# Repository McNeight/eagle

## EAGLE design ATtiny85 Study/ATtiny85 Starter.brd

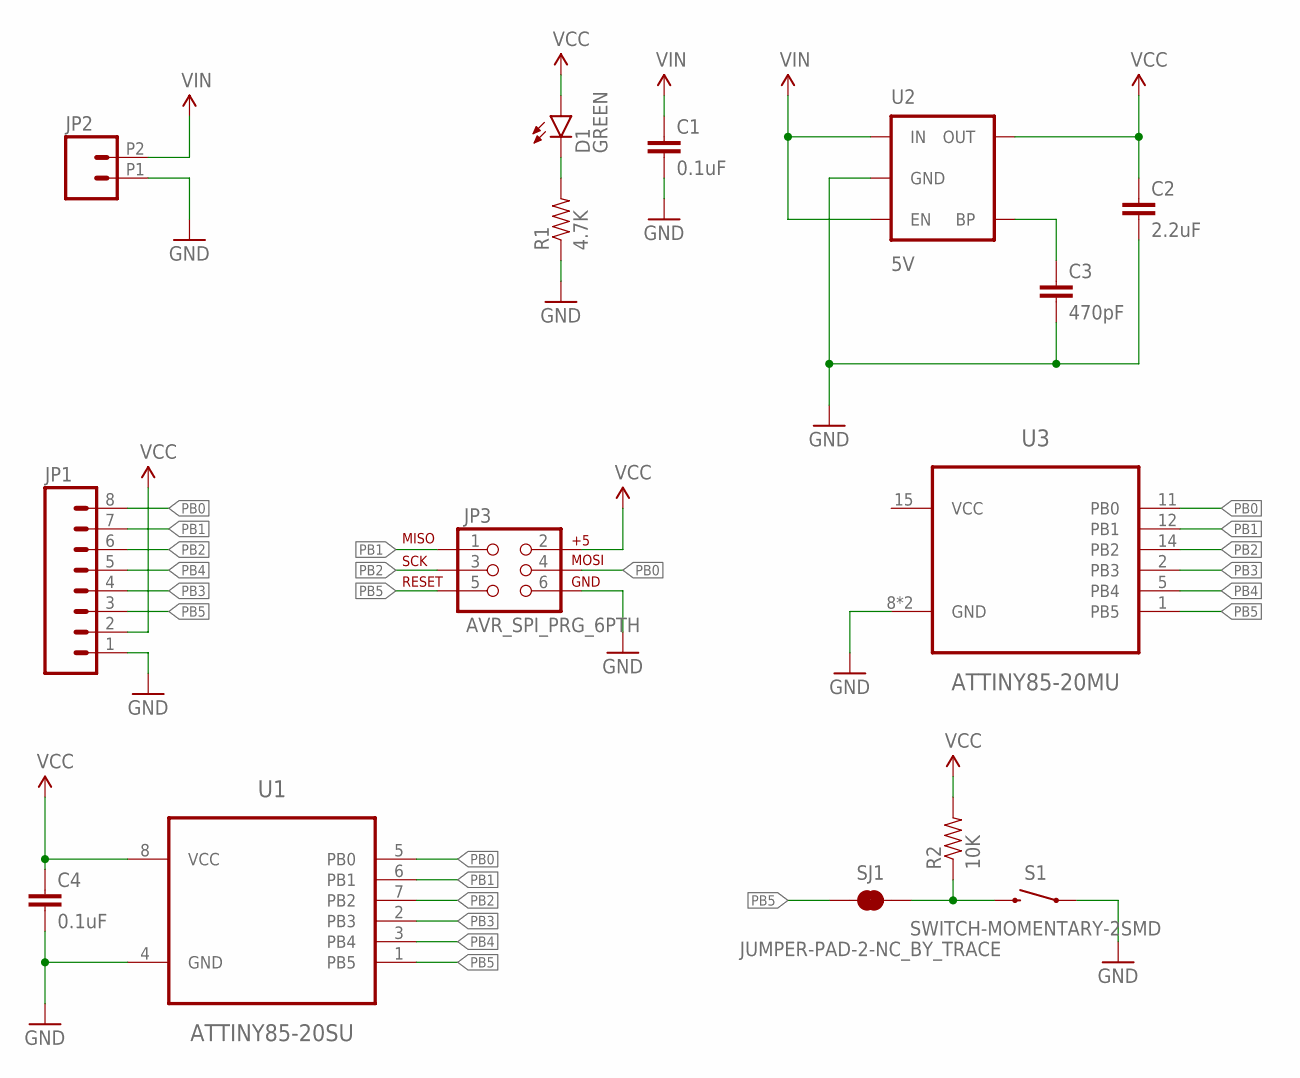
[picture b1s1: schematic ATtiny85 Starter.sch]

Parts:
C1, C4: 0.1uF; 0603-CAP
C2: 2.2uF; 0603-CAP
C3: 470pF; 0603-CAP
D1: GREEN; LED-0603
JP1: M08LOCK_NO_SILK; 1X08_LOCK_NO_SILK
JP2: M022.54MM_SCREWTERM; 1X02_2.54_SCREWTERM
JP3: AVR_SPI_PRG_6PTH; 2X3
R1: 4.7K; 0603-RES
R2: 10K; 0603-RES
S1: SWITCH-MOMENTARY-2SMD; TACTILE-SWITCH-SMD
SJ1: JUMPER-PAD-2-NC_BY_TRACE; PAD-JUMPER-2-NC_BY_TRACE_YES_SILK
U1: ATTINY85-20SU; 8S2
U2: 5V; SOT23-5
U3: ATTINY85-20MU; 20M1

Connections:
GND: C1.2, C2.2, C3.2, C4.2, JP1.1, JP2.P1 (1), JP3.6, R1.1, S1.1, U1.4 (GND), U2.2 (GND), U3.8 (GND), U3.PAD (GND)
unnamed: R2.1, S1.3 (2), SJ1.2
unnamed: D1.C, R1.2
unnamed: C3.1, U2.4 (BP)
PB0: JP1.8, JP3.4, U1.5 (PB0), U3.11 (PB0)
PB1: JP1.7, JP3.1, U1.6 (PB1), U3.12 (PB1)
PB2: JP1.6, JP3.3, U1.7 (PB2), U3.14 (PB2)
PB3: JP1.4, U1.2 (PB3), U3.2 (PB3)
PB4: JP1.5, U1.3 (PB4), U3.5 (PB4)
PB5: JP1.3, JP3.5, SJ1.1, U1.1 (PB5), U3.1 (PB5)
VCC: C2.1, C4.1, D1.A, JP1.2, JP3.2, R2.2, U1.8 (VCC), U2.5 (OUT), U3.15 (VCC)
VIN: C1.1, JP2.P2 (2), U2.1 (IN), U2.3 (EN)

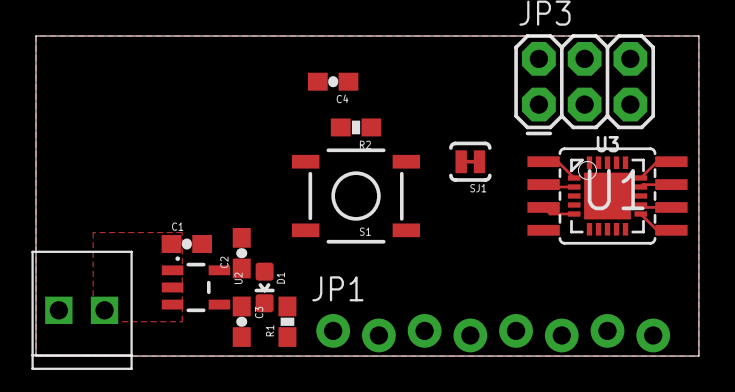
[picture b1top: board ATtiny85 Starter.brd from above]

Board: 2 copper layers, 36.8 x 17.8 mm, 15 parts (0 on the bottom side), 12 nets.

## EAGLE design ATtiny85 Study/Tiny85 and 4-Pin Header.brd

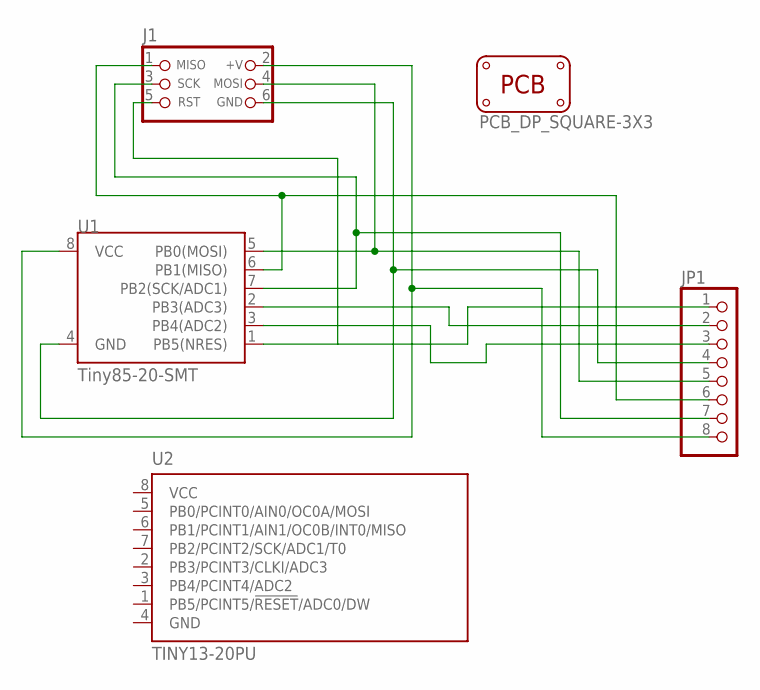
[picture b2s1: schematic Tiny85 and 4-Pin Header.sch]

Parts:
J1: CON_HEADER_PRG_AVR_ICSP-PTH; HEADER_PRG_2X03
JP1: PINHD-1X8CLEANBIG; 1X08-CLEANBIG
PCB1: PCB_DP_SQUARE-3X3; DP3030_V1
U1: Tiny85-20-SMT; SO08-EIAJ
U2: TINY13-20PU; 8P3

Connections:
GND: U2.4 (GND)
unnamed: J1.6 (GND), JP1.4, U1.4 (GND)
unnamed: J1.2 (+V), JP1.8, U1.8 (VCC)
unnamed: J1.3 (SCK), JP1.7, U1.7 (PB2(SCK/ADC1))
unnamed: J1.4 (MOSI), JP1.5, U1.5 (PB0(MOSI))
unnamed: JP1.2, U1.2 (PB3(ADC3))
unnamed: J1.5 (RST), JP1.1, U1.1 (PB5(NRES))
unnamed: J1.1 (MISO), JP1.6, U1.6 (PB1(MISO))
unnamed: JP1.3, U1.3 (PB4(ADC2))
VCC: U2.8 (VCC)

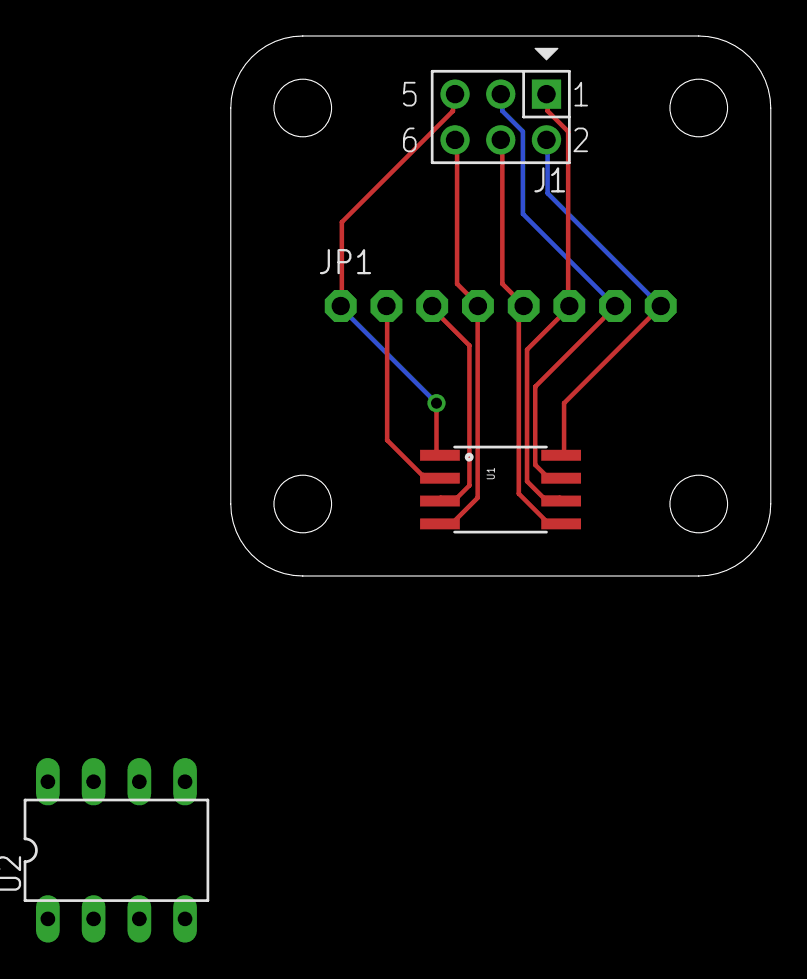
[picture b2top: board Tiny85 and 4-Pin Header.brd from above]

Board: 2 copper layers, 30.0 x 30.0 mm, 5 parts (0 on the bottom side), 8 nets.

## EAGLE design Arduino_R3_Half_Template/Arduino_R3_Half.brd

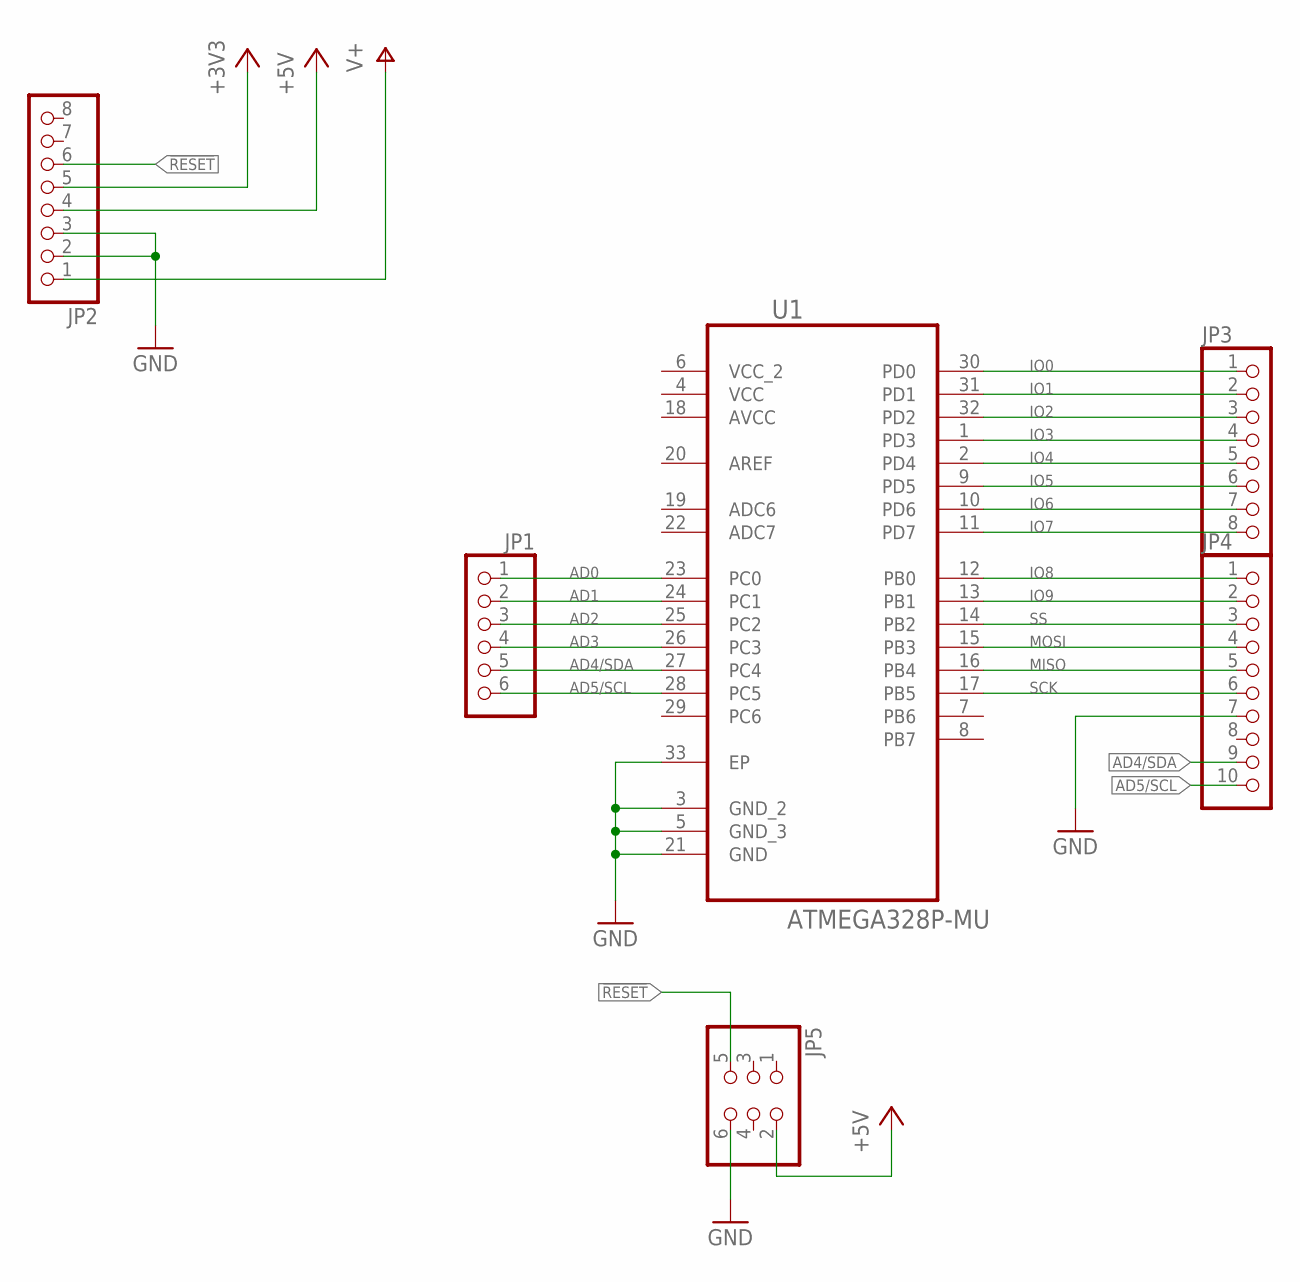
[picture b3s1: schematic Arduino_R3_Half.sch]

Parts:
JP1: PINHD-1X6; 1X06
JP2, JP3: PINHD-1X8; 1X08
JP4: PINHD-1X10; 1X10
JP5: PINHD-2X3; 2X03
U1: ATMEGA328P-MU; QFN50P500X500X100-33N

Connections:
!RESET: JP2.6, JP5.5
+3V3: JP2.5
+5V: JP2.4, JP5.2
AD0: JP1.1, U1.23 (PC0)
AD1: JP1.2, U1.24 (PC1)
AD2: JP1.3, U1.25 (PC2)
AD3: JP1.4, U1.26 (PC3)
AD4/SDA: JP1.5, JP4.9, U1.27 (PC4)
AD5/SCL: JP1.6, JP4.10, U1.28 (PC5)
AVCC: U1.18 (AVCC)
GND: JP2.2, JP2.3, JP4.7, JP5.6, U1.3 (GND_2), U1.5 (GND_3), U1.21 (GND), U1.33 (EP)
IO0: JP3.1, U1.30 (PD0)
IO1: JP3.2, U1.31 (PD1)
IO2: JP3.3, U1.32 (PD2)
IO3: JP3.4, U1.1 (PD3)
IO4: JP3.5, U1.2 (PD4)
IO5: JP3.6, U1.9 (PD5)
IO6: JP3.7, U1.10 (PD6)
IO7: JP3.8, U1.11 (PD7)
IO8: JP4.1, U1.12 (PB0)
IO9: JP4.2, U1.13 (PB1)
MISO: JP4.5, U1.16 (PB4)
MOSI: JP4.4, U1.15 (PB3)
SCK: JP4.6, U1.17 (PB5)
SS: JP4.3, U1.14 (PB2)
V+: JP2.1
VCC: U1.4 (VCC)
VCC_2: U1.6 (VCC_2)

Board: 2 copper layers, 6 parts (0 on the bottom side), 23 nets, no tracks yet.

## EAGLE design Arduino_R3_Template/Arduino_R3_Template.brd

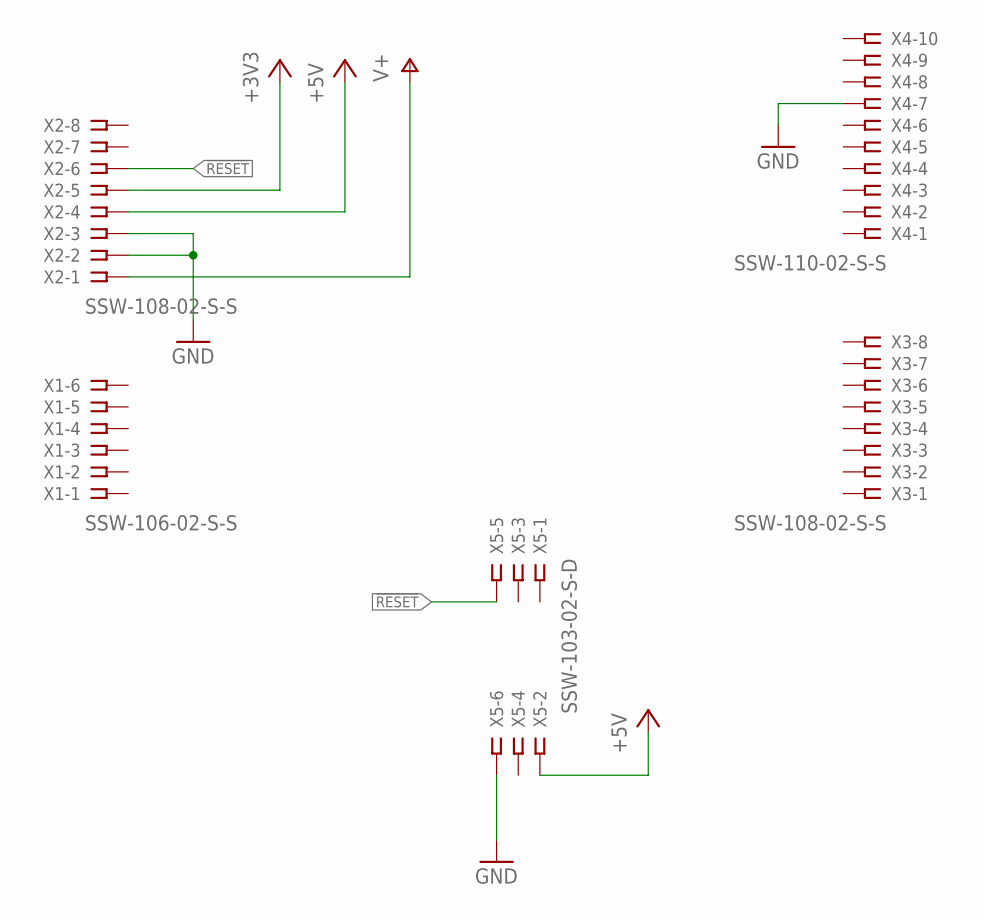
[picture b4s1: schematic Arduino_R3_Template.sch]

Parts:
X1: SSW-106-02-S-S
X2, X3: SSW-108-02-S-S
X4: SSW-110-02-S-S
X5: SSW-103-02-S-D

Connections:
!RESET: X2.6, X5.5
+3V3: X2.5
+5V: X2.4, X5.2
GND: X2.2, X2.3, X4.7, X5.6
V+: X2.1

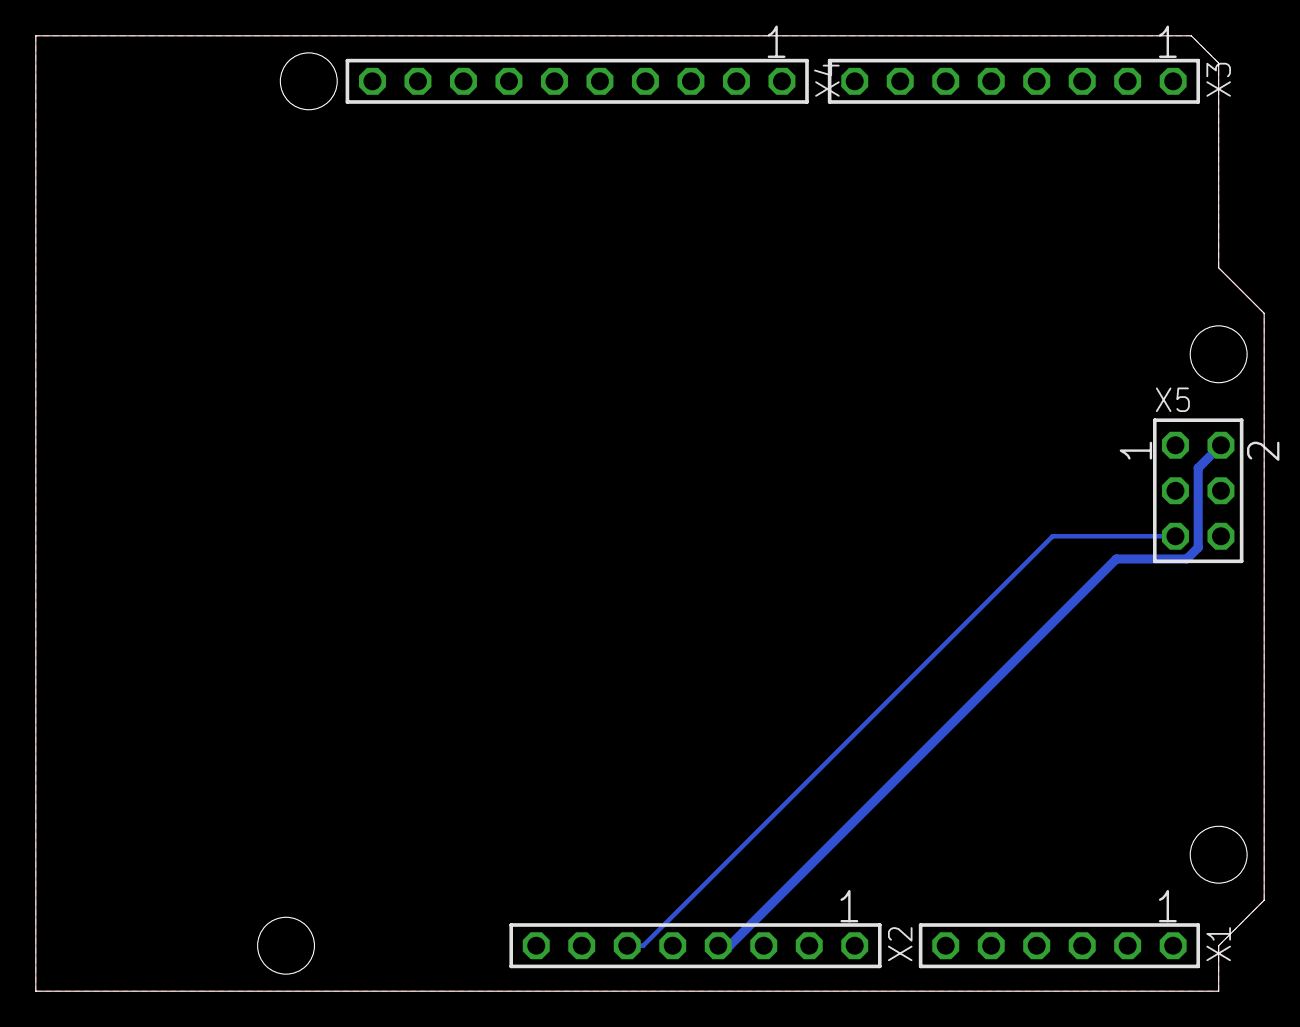
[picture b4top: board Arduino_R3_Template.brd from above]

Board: 2 copper layers, 68.6 x 53.3 mm, 5 parts (0 on the bottom side), 3 nets.

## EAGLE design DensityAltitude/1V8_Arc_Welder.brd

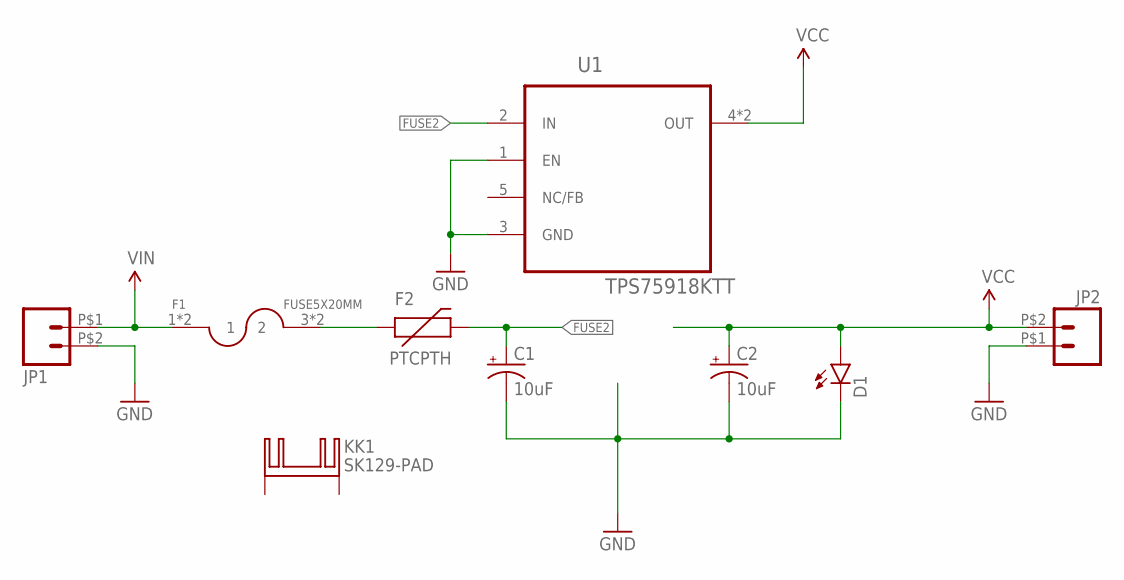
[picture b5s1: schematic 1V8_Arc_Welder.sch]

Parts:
C1, C2: 10uF; E2-5
D1: LED5MM
F1: FUSE5X20MM; FUSE_1A3399
F2: PTCPTH; PTC
JP1, JP2: M02TE-282834-2; 1X02_282834-2
KK1: SK129-PAD; SK129
U1: TPS75918KTT; TO263-5

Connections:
FUSE1: F1.3 (2), F1.4 (2), F2.P$1 (1)
FUSE2: C1.+, F2.P$2 (2), U1.2 (IN)
GND: C1.-, C2.-, D1.K (C), JP1.P$2 (2), JP2.P$1 (1), U1.1 (EN), U1.3 (GND)
VCC: C2.+, D1.A, JP2.P$2 (2), U1.4 (OUT), U1.6 (OUT)
VIN: F1.1, F1.2 (1), JP1.P$1 (1)

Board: 2 copper layers, 10 parts (0 on the bottom side), 5 nets, no tracks yet.

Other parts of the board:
U$1: OSHW-LOGO-S

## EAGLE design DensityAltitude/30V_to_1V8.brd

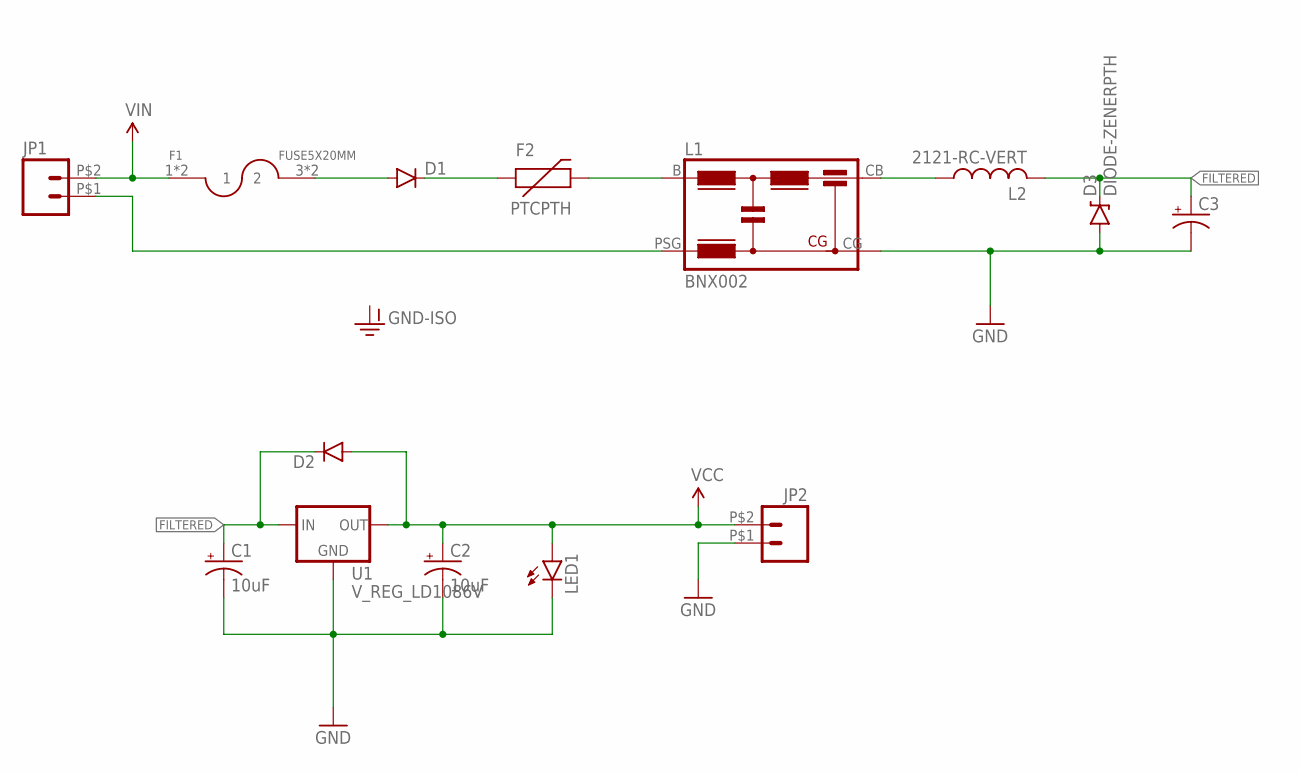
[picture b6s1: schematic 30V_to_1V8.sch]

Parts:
C1, C2: 10uF; E2-5
C3: CPOL-USE10-30; EB30D
D1, D2: DIODEPTH; DIODE-1N4001
D3: DIODE-ZENERPTH; DIODE-ZENER
F1: FUSE5X20MM; FUSE_1A3399
F2: PTCPTH; PTC
JP1, JP2: M02TE-282834-2; 1X02_282834-2
L1: BNX002
L2: 2121-RC-VERT
LED1: LED5MM
U1: V_REG_LD1086V; TO-220-SINGLE

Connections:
DIODE1: D1.C, F2.P$1 (1)
FILTERED: C1.+, C3.+, D2.C, D3.P$1 (C), L2.2, U1.IN
FUSE1: D1.A, F1.3 (2), F1.4 (2)
FUSE2: F2.P$2 (2), L1.B
GND: C1.-, C2.-, C3.-, D3.P$2 (A), JP2.P$1 (1), L1.CG, LED1.K (C), U1.GND
unnamed: L1.CB, L2.1
unnamed: JP1.P$1 (1), L1.PSG
VCC: C2.+, D2.A, JP2.P$2 (2), LED1.A, U1.OUT
VIN: F1.1, F1.2 (1), JP1.P$2 (2)

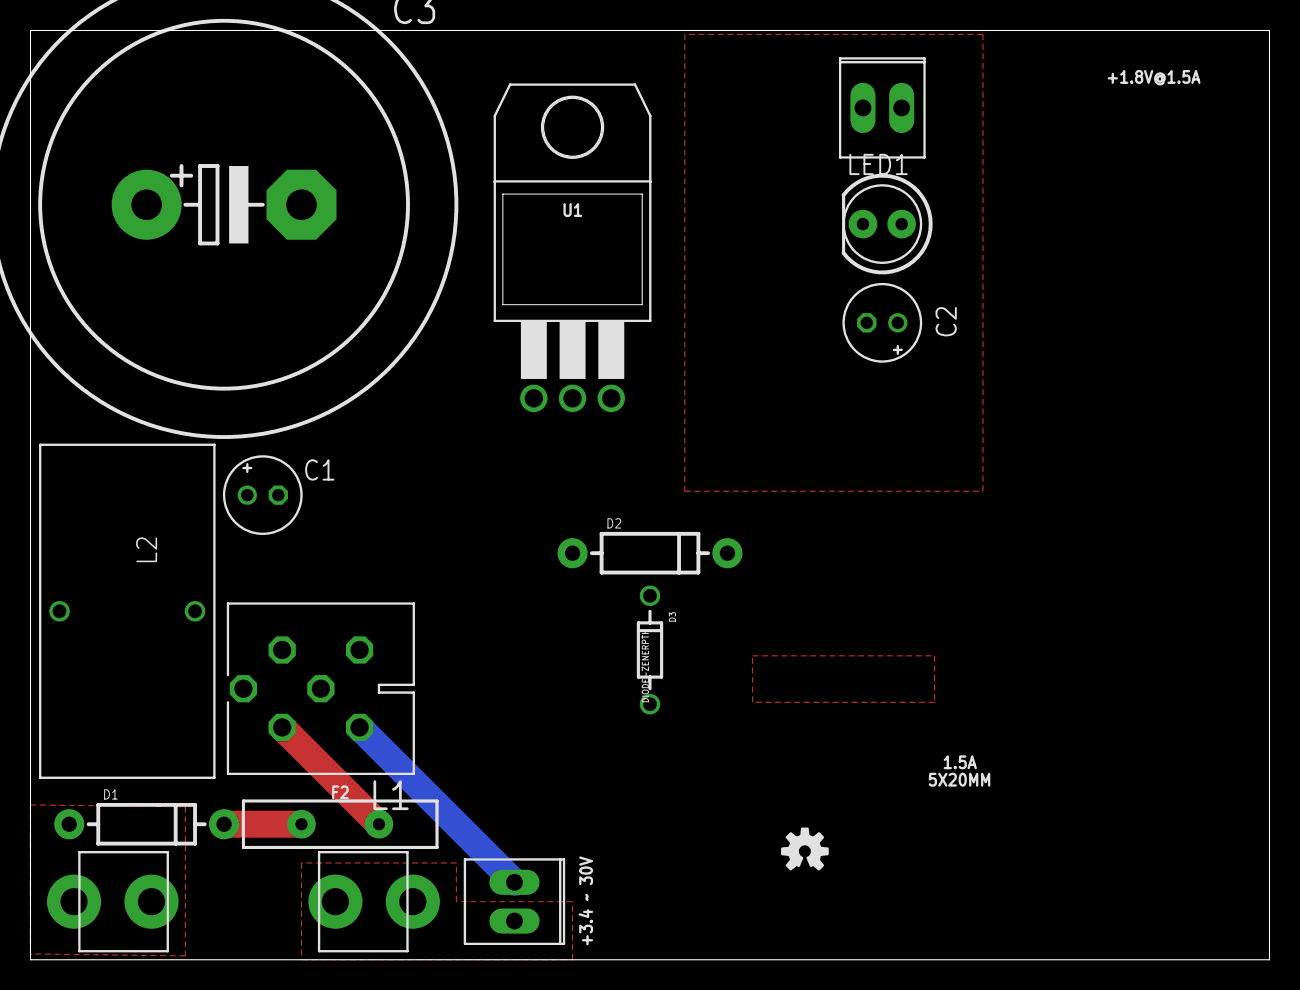
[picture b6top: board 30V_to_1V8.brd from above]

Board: 2 copper layers, 81.3 x 61.0 mm, 15 parts (0 on the bottom side), 9 nets.

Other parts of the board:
U$1: OSHW-LOGO-S

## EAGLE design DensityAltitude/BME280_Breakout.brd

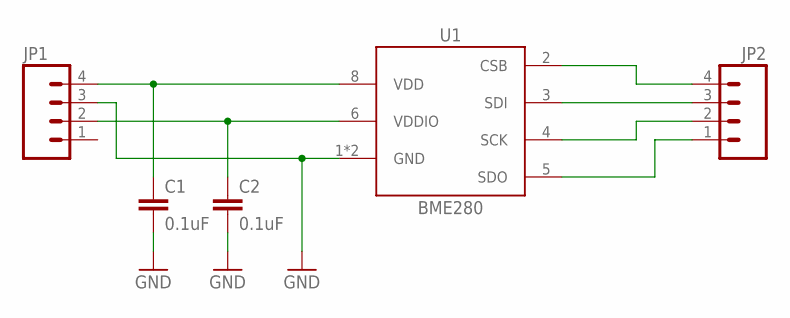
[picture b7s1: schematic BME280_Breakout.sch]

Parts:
C1, C2: 0.1uF; 0402-CAP
JP1, JP2: M04NO_SILK_ALL_ROUND; 1X04_NO_SILK_ALL_ROUND
U1: BME280

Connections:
GND: C1.2, C2.2, JP1.3, U1.1 (GND), U1.7 (GND)
unnamed: C1.1, JP1.4, U1.8 (VDD)
unnamed: C2.1, JP1.2, U1.6 (VDDIO)
unnamed: JP2.3, U1.3 (SDI)
unnamed: JP2.2, U1.4 (SCK)
unnamed: JP2.1, U1.5 (SDO)
unnamed: JP2.4, U1.2 (CSB)

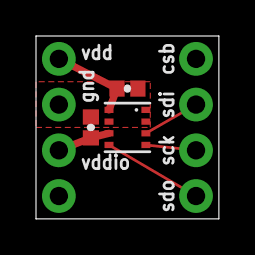
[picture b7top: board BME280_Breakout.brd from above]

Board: 2 copper layers, 10.2 x 10.2 mm, 6 parts (1 on the bottom side), 7 nets.

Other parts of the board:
U$1: OSHW-LOGO-S

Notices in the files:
parts and their libraries:
SparkFun-Resistors: Licensing: Creative Commons ShareAlike 4.0 International - https://creativecommons.org/licenses/by-sa/4.0
SparkFun-DigitalIC: Licensing: CC v3.0 Share-Alike You are welcome to use this library for commercial purposes.
